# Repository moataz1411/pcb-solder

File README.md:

# pcb-solder

A simple custom shaped PCB designed as a shark keychain with blink led and 555 timer.

The goal of the project was to combine electronic circuit with a creative PCB shape to make a cool keychain.

---

## Bill of Materials

| Component | Value | Qty |
|-----------|-------|-----|
| CR2032 Battery Holder | 3V | 1 |
| 5mm LED | Red | 1 |
| Resistor | 4.7kΩ | 2 |
| Resistor | 47kΩ | 1 |
| Resistor | 220Ω | 1 |
| Push Button | 6mm | 1 |
| 555 timer | -- | 1 |
| capacitor | 10uF | 1 |

**Total: 9 components**

---

schematic photo

---

pcb photo

---

3d view

--- 

photo in jlcpcb

---

# my user  : mozmezo

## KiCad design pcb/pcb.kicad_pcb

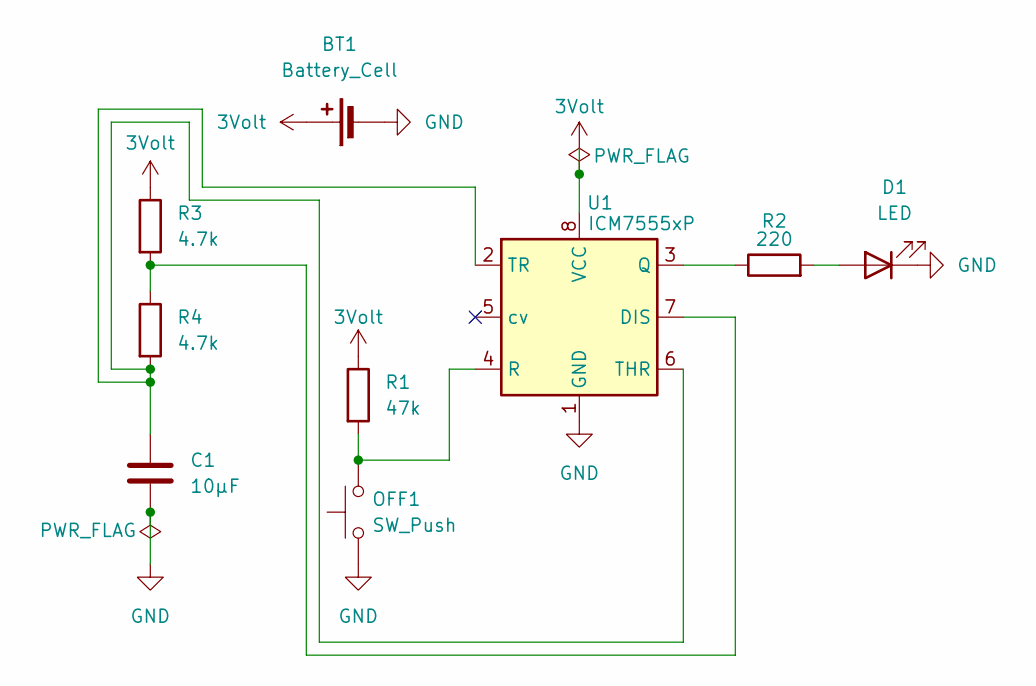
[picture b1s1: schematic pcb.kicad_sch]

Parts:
BT1: Battery_Cell; BatteryHolder_Keystone_3034_1x20mm
C1: 10µF; CP_Radial_D8.0mm_P5.00mm
D1: LED; LED_D5.0mm
OFF1: SW_Push; SW_PUSH_6mm
R1: 47k; R_Axial_DIN0207_L6.3mm_D2.5mm_P7.62mm_Horizontal
R2: 220; R_Axial_DIN0207_L6.3mm_D2.5mm_P7.62mm_Horizontal
R3, R4: 4.7k; R_Axial_DIN0207_L6.3mm_D2.5mm_P7.62mm_Horizontal
U1: ICM7555xP; DIP-8_W7.62mm

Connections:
3Volt: BT1.1 (+), R1.1, R3.1, U1.8 (VCC)
GND: BT1.2 (-), C1.2, D1.1 (K), OFF1.1, U1.1 (GND)
unnamed: D1.2 (A), R2.2
unnamed: R3.2, R4.1, U1.7 (DIS)
unnamed: R2.1, U1.3 (Q)
unnamed: OFF1.2, R1.2, U1.4 (R)
unnamed: C1.1, R4.2, U1.2 (TR), U1.6 (THR)

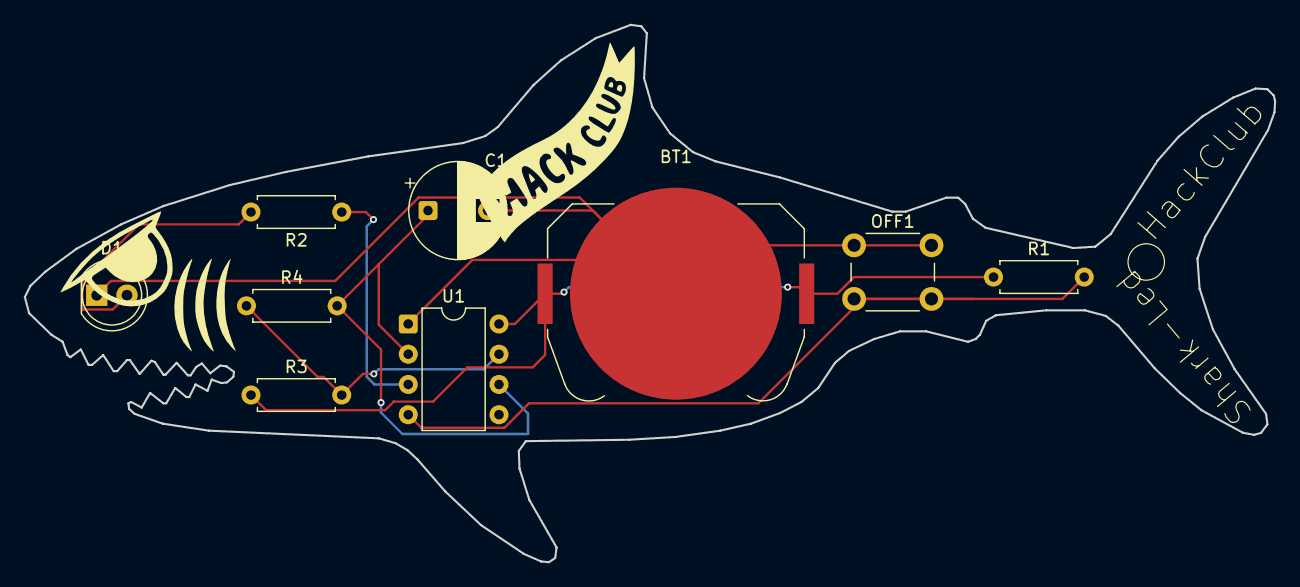
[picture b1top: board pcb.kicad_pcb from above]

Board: 2 copper layers, 105.0 x 45.1 mm, 9 parts (0 on the bottom side), 7 nets.
